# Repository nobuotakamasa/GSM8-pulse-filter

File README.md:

# GSM8-pulse-filter
pulse filter for GSM8

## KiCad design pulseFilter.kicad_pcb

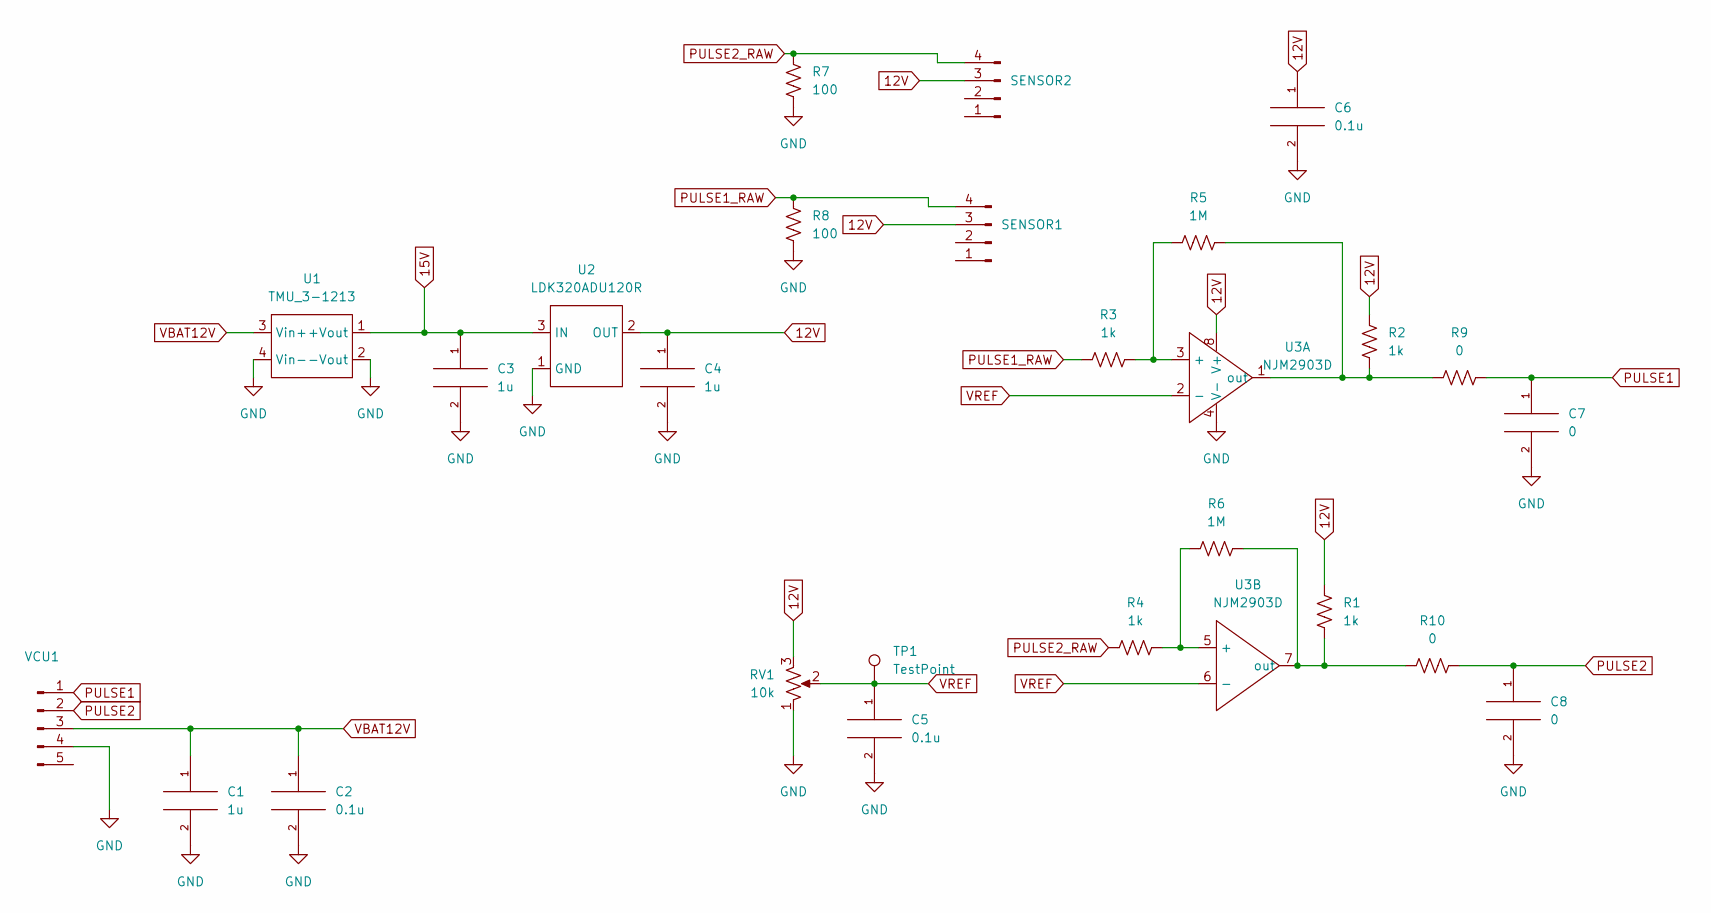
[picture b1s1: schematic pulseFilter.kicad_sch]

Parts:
C1, C3, C4: 1u; C_0603_1608Metric_Pad1.08x0.95mm_HandSolder
C2, C5, C6: 0.1u; C_0603_1608Metric_Pad1.08x0.95mm_HandSolder
C7, C8: 0; C_0603_1608Metric_Pad1.08x0.95mm_HandSolder
R1, R2, R3, R4: 1k; R_0603_1608Metric_Pad0.98x0.95mm_HandSolder
R5, R6: 1M; R_0603_1608Metric_Pad0.98x0.95mm_HandSolder
R7, R8: 100; R_0603_1608Metric_Pad0.98x0.95mm_HandSolder
R9, R10: 0; R_0603_1608Metric_Pad0.98x0.95mm_HandSolder
RV1: 10k; Potentiometer_Bourns_3296W_Vertical
SENSOR1, SENSOR2: Conn_01x04_Male; JST_XA_S04B-XASK-1N-BN_1x04_P2.50mm_Horizontal
TP1: TestPoint; TestPoint_Loop_D1.80mm_Drill1.0mm_Beaded
U1: TMU_3-1213; TRACO POWER DCDC
U2: LDK320ADU120R; SOT-23-3
U3: NJM2903D; DIP-8_W7.62mm
VCU1: Conn_01x05_Male; JST_XA_S05B-XASK-1N-BN_1x05_P2.50mm_Horizontal

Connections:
12V: C4.1, C6.1, R1.1, R2.1, RV1.3, SENSOR1.3, SENSOR2.3, U2.2 (OUT), U3.8 (V+)
15V: C3.1, U1.1 (+Vout), U2.3 (IN)
GND: C1.2, C2.2, C3.2, C4.2, C5.2, C6.2, C7.2, C8.2, R7.1, R8.1, RV1.1, U1.2 (-Vout), U1.4 (Vin-), U2.1 (GND), U3.4 (V-), VCU1.4
unnamed: R1.2, R6.2, R10.1, U3.7 (out)
unnamed: R2.2, R5.2, R9.1, U3.1 (out)
unnamed: R3.2, R5.1, U3.3 (+)
unnamed: R4.2, R6.1, U3.5 (+)
PULSE1: C7.1, R9.2, VCU1.1
PULSE1_RAW: R3.1, R8.2, SENSOR1.4
PULSE2: C8.1, R10.2, VCU1.2
PULSE2_RAW: R4.1, R7.2, SENSOR2.4
VBAT12V: C1.1, C2.1, U1.3 (Vin+), VCU1.3
VREF: C5.1, RV1.2, TP1.1, U3.2 (-), U3.6 (-)

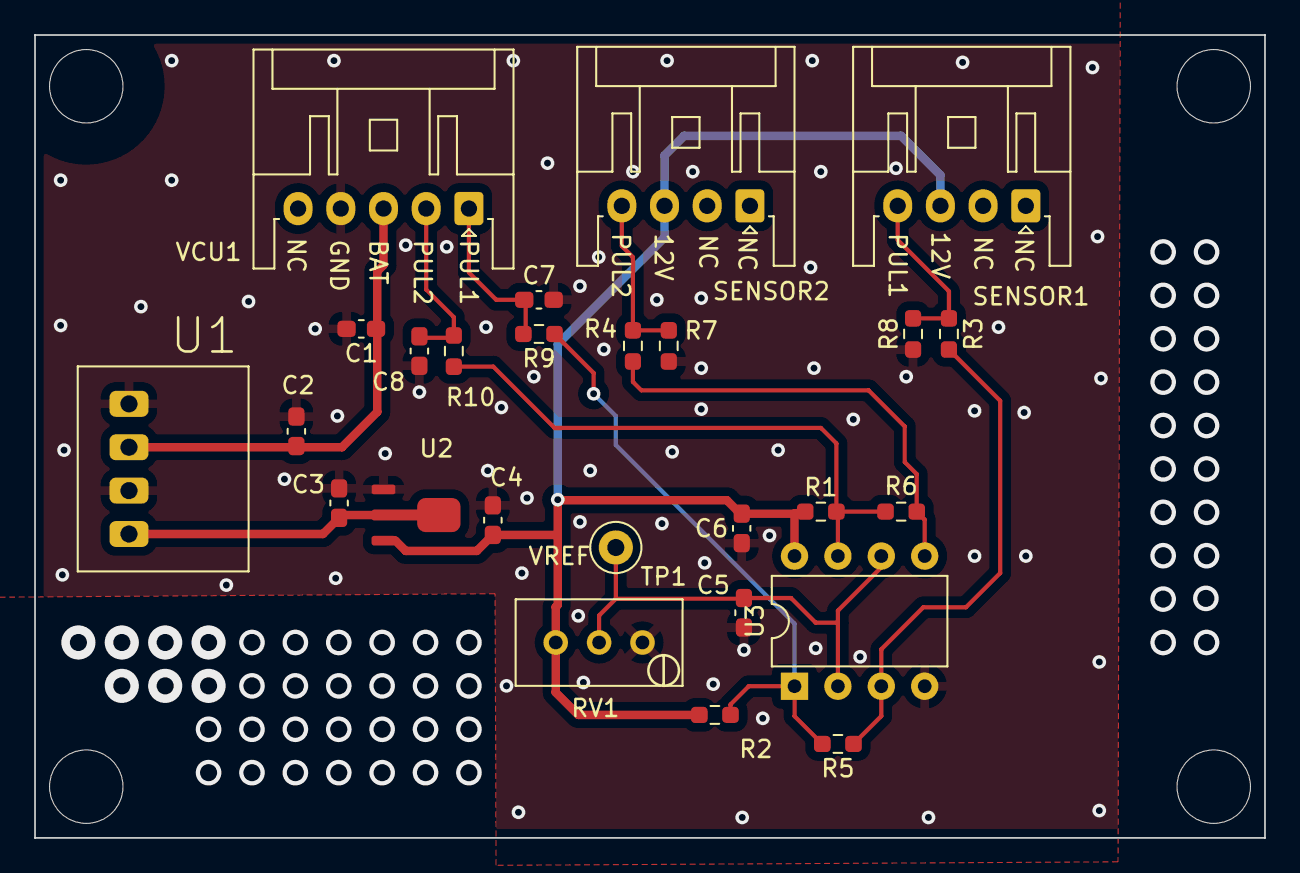
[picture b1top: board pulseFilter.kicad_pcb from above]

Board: 2 copper layers, 72.0 x 47.0 mm, 26 parts (0 on the bottom side), 13 nets.

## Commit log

2023-03-14 to chip resistors
2023-03-14 backup
2023-03-14 add silk
2023-04-04 bug fix
